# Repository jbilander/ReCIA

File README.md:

# ReCIA
A drop in replacement CIA (8520) for old Amiga Computers

This is WORK IN PROGRESS. If you generate gerbers and order PCBs from this source you are doing so completely at your own risk!.

Current design is based on an intel/altera 10 Max FPGA but this is mostly so we can signal tap and record how a real 8520 behaves.
The oscillator on board is 10 MHz and the PLL on the Max 10 can take this clock and make a perfect 28.375 MHz or a 28.636 MHz clock signal which will be nice to base the logic on instead of the E-CLK.

The final design will probably target a `LCMXO2-640HC-4SG48C` FPGA or a microcontroller such as `AVR128DA64` or a `RP2350`.

When the DIP-version is functional a PLCC-version (for big box Amigas) can be made.

***

<br />

<br />

<br />

***

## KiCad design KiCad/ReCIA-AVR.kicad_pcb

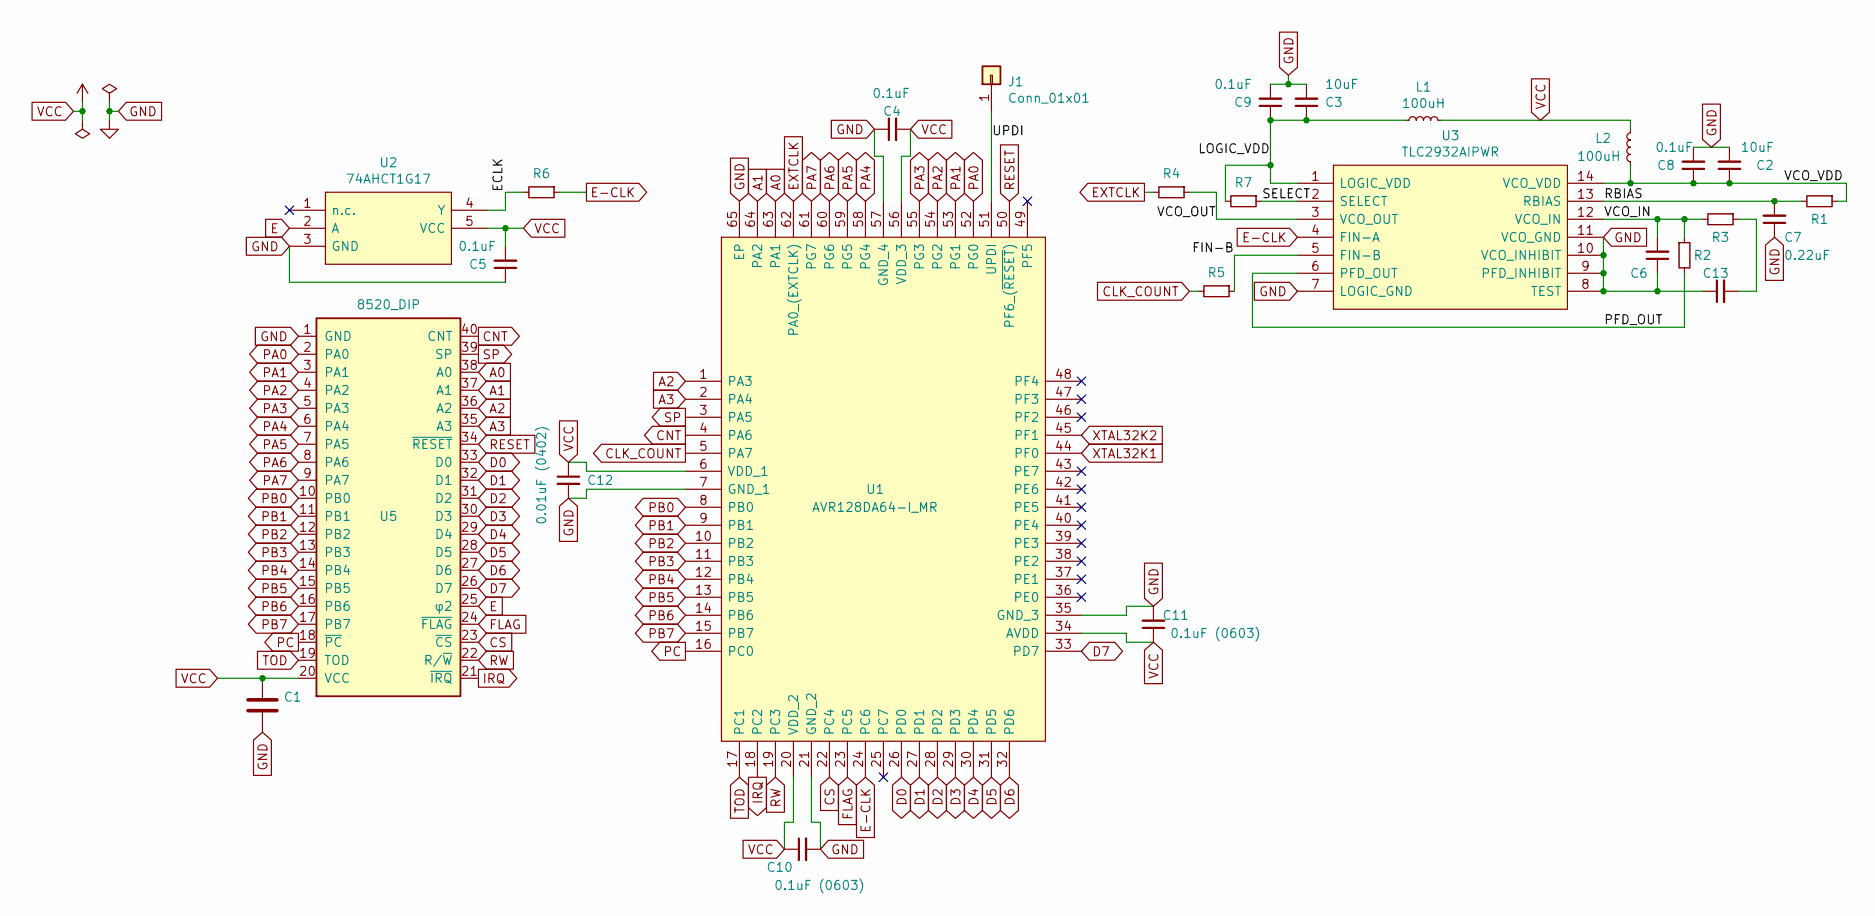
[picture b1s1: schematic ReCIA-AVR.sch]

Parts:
C1: C; C_1206_3216Metric_Pad1.33x1.80mm_HandSolder
C2, C3: 10uF; C_1206_3216Metric_Pad1.33x1.80mm_HandSolder
C4, C5, C6, C8, C9, C13: 0.1uF; C_0603_1608Metric_Pad1.08x0.95mm_HandSolder
C7: 0.22uF; C_0603_1608Metric_Pad1.08x0.95mm_HandSolder
C10, C11: 0.1uF (0603); C_0603_1608Metric_Pad1.08x0.95mm_HandSolder
C12: 0.01uF (0402); C_0402_1005Metric
J1: Conn_01x01; PinHeader_1x01_P2.54mm_Vertical
L1, L2: 100uH; L_0805_2012Metric_Pad1.15x1.40mm_HandSolder
R1: 3k3; R_0603_1608Metric_Pad0.98x0.95mm_HandSolder
R2, R3, R4, R5, R6: 33; R_0603_1608Metric_Pad0.98x0.95mm_HandSolder
R7: 10k; R_0603_1608Metric_Pad0.98x0.95mm_HandSolder
U1: AVR128DA64-I_MR; QFN-64-1EP_9x9mm_P0.5mm_EP7.15x7.15mm_ThermalVias
U2: 74AHCT1G17; SOT95P275X110-5N
U3: TLC2932AIPWR; TSSOP-14_4.4x5mm_P0.65mm
U5: 8520_DIP; DIP-40_W15.24mm

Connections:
/ECLK: R6.2, U2.4 (Y)
/FIN-B: R5.1, U3.5 (FIN-B)
/LOGIC_VDD: C3.1, C9.1, L1.1, R7.2, U3.1 (LOGIC_VDD)
/PFD_OUT: R2.2, U3.6 (PFD_OUT)
/RBIAS: C7.2, R1.2, U3.13 (RBIAS)
/SELECT: R7.1, U3.2 (SELECT)
/UPDI: J1.1, U1.51 (UPDI)
/VCO_IN: C6.2, R2.1, R3.2, U3.12 (VCO_IN)
/VCO_OUT: R4.1, U3.3 (VCO_OUT)
/VCO_VDD: C2.1, C8.1, L2.1, R1.1, U3.14 (VCO_VDD)
A0: U1.63 (PA1), U5.38 (A0)
A1: U1.64 (PA2), U5.37 (A1)
A2: U1.1 (PA3), U5.36 (A2)
A3: U1.2 (PA4), U5.35 (A3)
CLK_COUNT: R5.2, U1.5 (PA7)
CNT: U1.4 (PA6), U5.40 (CNT)
CS: U1.22 (PC4), U5.23 (~CS)
D0: U1.26 (PD0), U5.33 (D0)
D1: U1.27 (PD1), U5.32 (D1)
D2: U1.28 (PD2), U5.31 (D2)
D3: U1.29 (PD3), U5.30 (D3)
D4: U1.30 (PD4), U5.29 (D4)
D5: U1.31 (PD5), U5.28 (D5)
D6: U1.32 (PD6), U5.27 (D6)
D7: U1.33 (PD7), U5.26 (D7)
E: U2.2 (A), U5.25 (φ2)
E-CLK: R6.1, U1.24 (PC6), U3.4 (FIN-A)
EXTCLK: R4.2, U1.62 (PA0_(EXTCLK))
FLAG: U1.23 (PC5), U5.24 (~FLAG)
GND: C1.2, C2.2, C3.2, C4.1, C5.1, C6.1, C7.1, C8.2, C9.2, C10.2, C11.2, C12.2, C13.1, U1.7 (GND_1), U1.21 (GND_2), U1.35 (GND_3), U1.57 (GND_4), U1.65 (EP), U2.3 (GND), U3.7 (LOGIC_GND), U3.8 (TEST), U3.9 (PFD_INHIBIT), U3.10 (VCO_INHIBIT), U3.11 (VCO_GND), U5.1 (GND)
IRQ: U1.18 (PC2), U5.21 (~IRQ)
unnamed: C13.2, R3.1
PA0: U1.52 (PG0), U5.2 (PA0)
PA1: U1.53 (PG1), U5.3 (PA1)
PA2: U1.54 (PG2), U5.4 (PA2)
PA3: U1.55 (PG3), U5.5 (PA3)
PA4: U1.58 (PG4), U5.6 (PA4)
PA5: U1.59 (PG5), U5.7 (PA5)
PA6: U1.60 (PG6), U5.8 (PA6)
PA7: U1.61 (PG7), U5.9 (PA7)
PB0: U1.8 (PB0), U5.10 (PB0)
PB1: U1.9 (PB1), U5.11 (PB1)
PB2: U1.10 (PB2), U5.12 (PB2)
PB3: U1.11 (PB3), U5.13 (PB3)
PB4: U1.12 (PB4), U5.14 (PB4)
PB5: U1.13 (PB5), U5.15 (PB5)
PB6: U1.14 (PB6), U5.16 (PB6)
PB7: U1.15 (PB7), U5.17 (PB7)
PC: U1.16 (PC0), U5.18 (~PC)
RESET: U1.50 (PF6_(~RESET)), U5.34 (~RESET)
RW: U1.19 (PC3), U5.22 (R/~W)
SP: U1.3 (PA5), U5.39 (SP)
TOD: U1.17 (PC1), U5.19 (TOD)
VCC: C1.1, C4.2, C5.2, C10.1, C11.1, C12.1, L1.2, L2.2, U1.6 (VDD_1), U1.20 (VDD_2), U1.34 (AVDD), U1.56 (VDD_3), U2.5 (VCC), U5.20 (VCC)
XTAL32K1: U1.44 (PF0)
XTAL32K2: U1.45 (PF1)

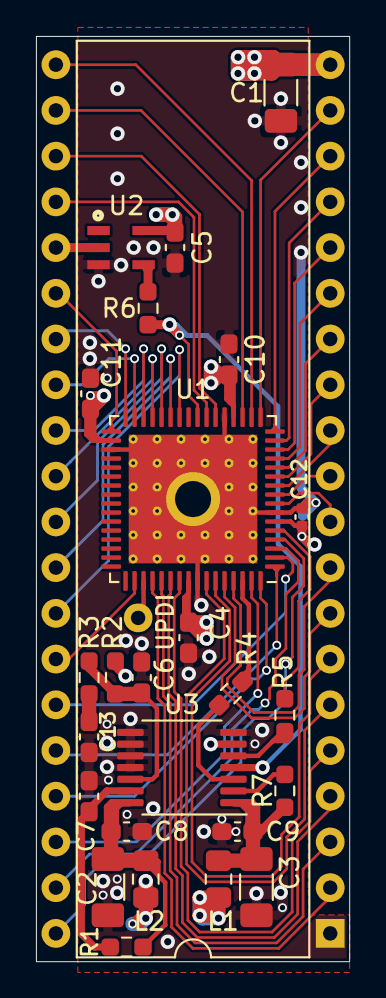
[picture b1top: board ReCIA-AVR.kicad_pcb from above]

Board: 4 copper layers, 17.4 x 51.4 mm, 27 parts (0 on the bottom side), 54 nets.

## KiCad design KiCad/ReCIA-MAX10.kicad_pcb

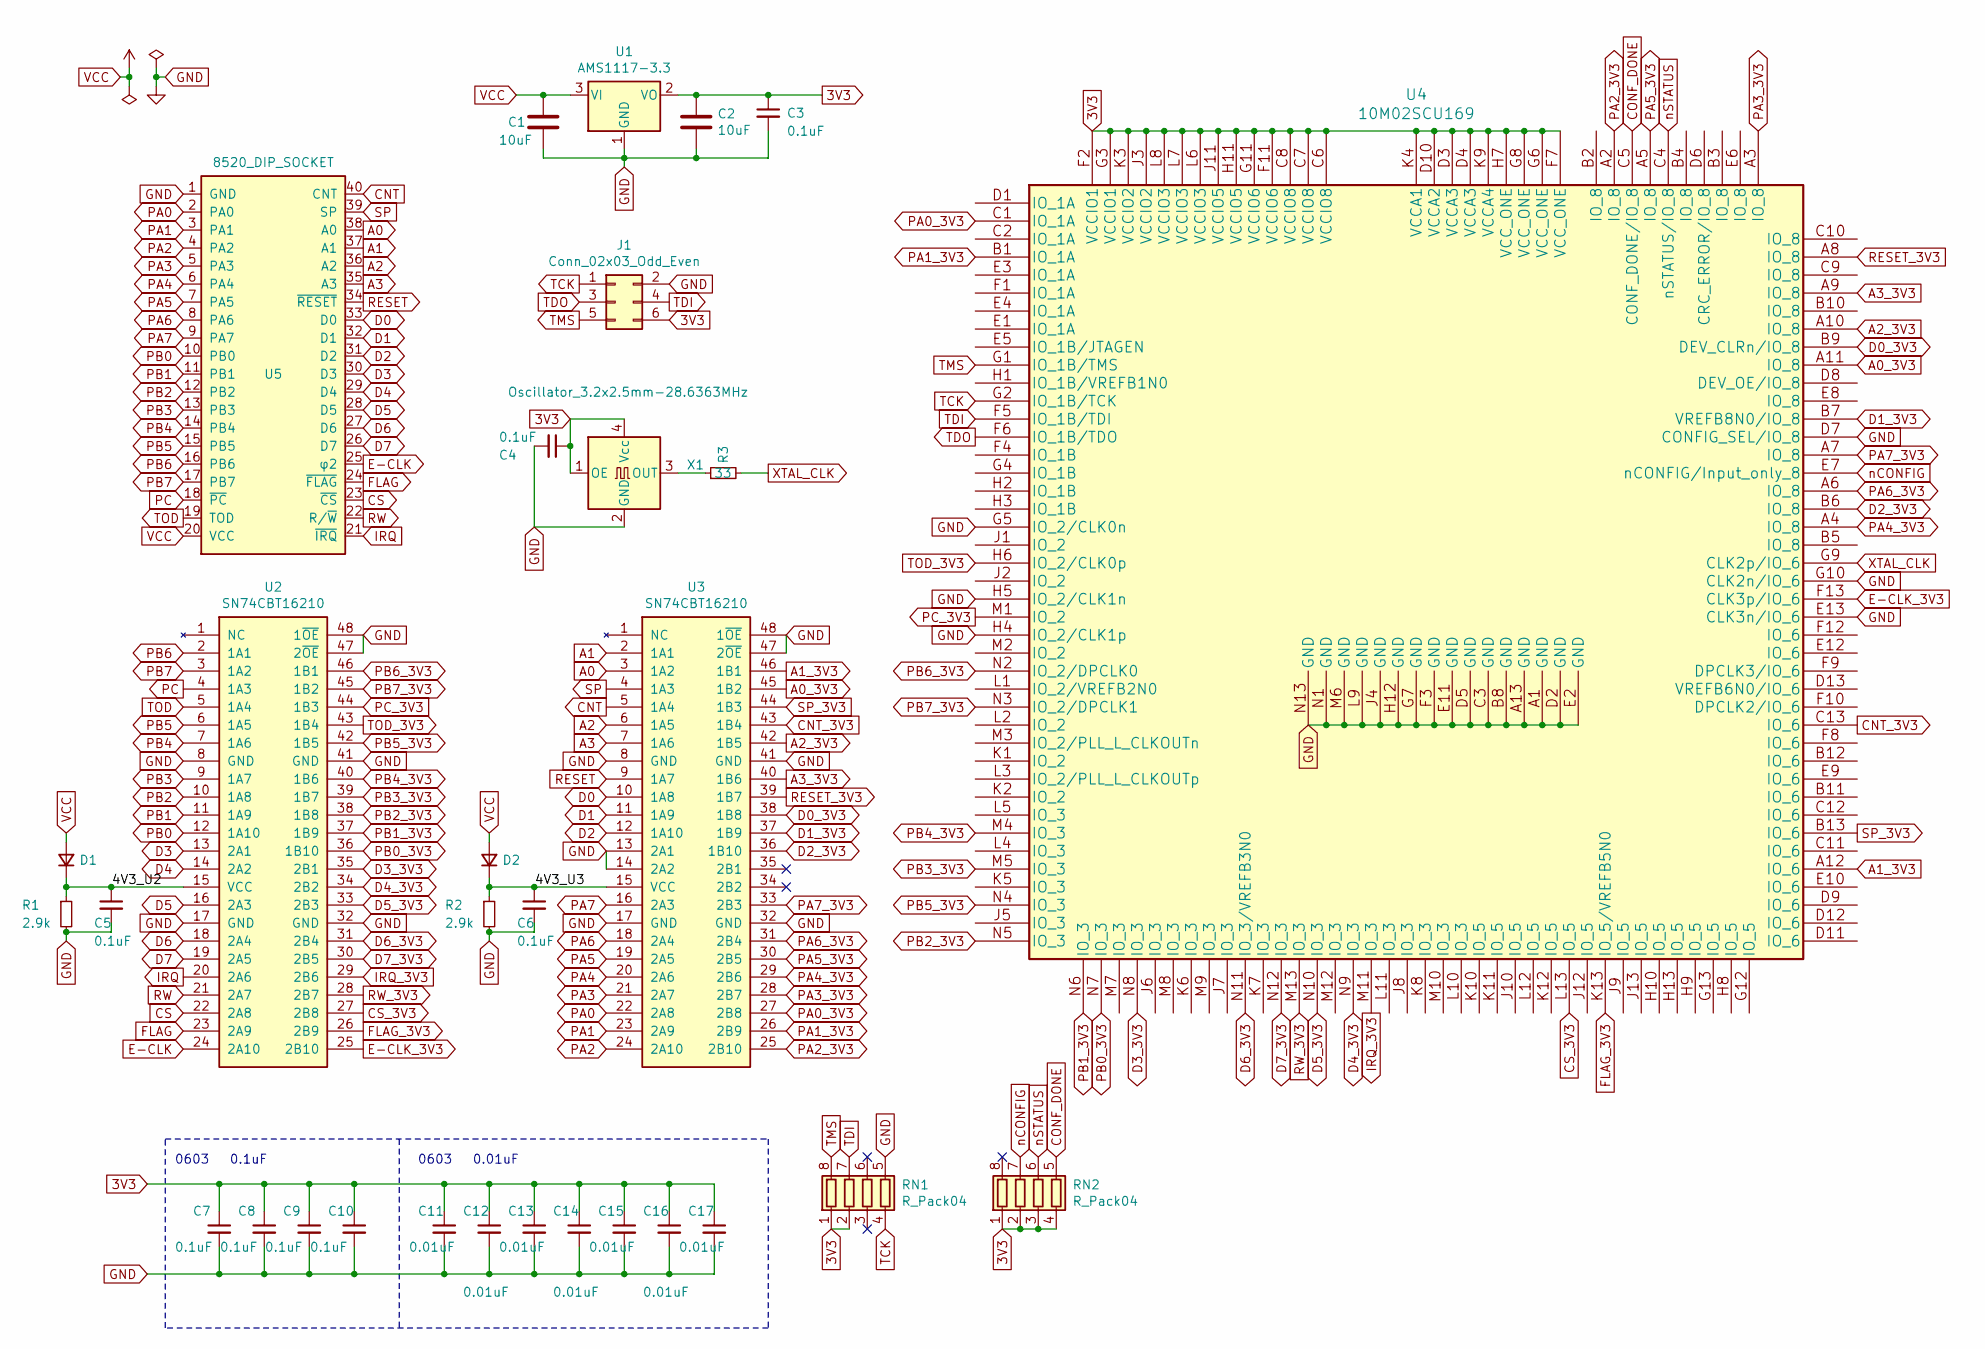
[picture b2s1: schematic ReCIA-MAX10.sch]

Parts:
C1, C2: 10uF; C_1206_3216Metric_Pad1.33x1.80mm_HandSolder
C3: 0.1uF; C_0805_2012Metric_Pad1.18x1.45mm_HandSolder
C4: 0.1uF; C_0805_2012Metric
C5, C6, C7, C8, C9: 0.1uF; C_0603_1608Metric_Pad1.08x0.95mm_HandSolder
C10: 0.1uF; C_0603_1608Metric
C11, C12, C13, C14, C15: 0.01uF; C_0603_1608Metric_Pad1.08x0.95mm_HandSolder
C16, C17: 0.01uF; C_0603_1608Metric
D1, D2: D_Small; D_0603_1608Metric_Pad1.05x0.95mm_HandSolder
J1: Conn_02x03_Odd_Even; PinHeader_2x03_P2.00mm_Vertical_SMD
R1, R2: 2.9k; R_0603_1608Metric_Pad0.98x0.95mm_HandSolder
R3: 33; R_0603_1608Metric_Pad0.98x0.95mm_HandSolder
RN1, RN2: R_Pack04; RESCAF80P320X160X60-8N
U1: AMS1117-3.3; SOT-223-3_TabPin2
U2, U3: SN74CBT16210; TSSOP-48_4.4x9.7mm_P0.4mm
U4: 10M02SCU169; BGA-169_11.0x11.0mm_Layout13x13_P0.8mm_Ball0.5mm_Pad0.35mm_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
U5: 8520_DIP_SOCKET; DIP-40_W15.24mm
X1: Oscillator_3.2x2.5mm-28.6363MHz; Oscillator_SMD_SeikoEpson_SG8002CE-4Pin_3.2x2.5mm

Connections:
3V3: C2.1, C3.1, C4.1, C7.1, C8.1, C9.1, C10.1, C11.1, C12.1, C13.1, C14.1, C15.1, C16.1, C17.1, J1.6, RN1.1 (R1.1), RN1.2 (R2.1), RN2.1 (R1.1), RN2.2 (R2.1), RN2.3 (R3.1), RN2.4 (R4.1), U1.2 (VO), U4.C6 (VCCIO8), U4.C7 (VCCIO8), U4.C8 (VCCIO8), U4.D3 (VCCA3), U4.D4 (VCCA3), U4.D10 (VCCA2), U4.F2 (VCCIO1), U4.F7 (VCC_ONE), U4.F11 (VCCIO6), U4.G3 (VCCIO1), U4.G6 (VCC_ONE), U4.G8 (VCC_ONE), U4.G11 (VCCIO6), U4.H7 (VCC_ONE), U4.H11 (VCCIO5), U4.J3 (VCCIO2), U4.J11 (VCCIO5), U4.K3 (VCCIO2), U4.K4 (VCCA1), U4.K9 (VCCA4), U4.L6 (VCCIO3), U4.L7 (VCCIO3), U4.L8 (VCCIO3), X1.1 (OE), X1.4 (Vcc)
/4V3_U2: C5.1, D1.1 (K), R1.1, U2.15 (VCC)
/4V3_U3: C6.1, D2.1 (K), R2.1, U3.15 (VCC)
A0: U3.3 (1A2), U5.38 (A0)
A0_3V3: U3.45 (1B2), U4.A11 (IO_8)
A1: U3.2 (1A1), U5.37 (A1)
A1_3V3: U3.46 (1B1), U4.A12 (IO_6)
A2: U3.6 (1A5), U5.36 (A2)
A2_3V3: U3.42 (1B5), U4.A10 (IO_8)
A3: U3.7 (1A6), U5.35 (A3)
A3_3V3: U3.40 (1B6), U4.A9 (IO_8)
CNT: U3.5 (1A4), U5.40 (CNT)
CNT_3V3: U3.43 (1B4), U4.C13 (IO_6)
CONF_DONE: RN2.5 (R4.2), U4.C5 (CONF_DONE/IO_8)
CS: U2.22 (2A8), U5.23 (~CS)
CS_3V3: U2.27 (2B8), U4.L13 (IO_5)
D0: U3.10 (1A8), U5.33 (D0)
D0_3V3: U3.38 (1B8), U4.B9 (DEV_CLRn/IO_8)
D1: U3.11 (1A9), U5.32 (D1)
D1_3V3: U3.37 (1B9), U4.B7 (VREFB8N0/IO_8)
D2: U3.12 (1A10), U5.31 (D2)
D2_3V3: U3.36 (1B10), U4.B6 (IO_8)
D3: U2.13 (2A1), U5.30 (D3)
D3_3V3: U2.35 (2B1), U4.N8 (IO_3)
D4: U2.14 (2A2), U5.29 (D4)
D4_3V3: U2.34 (2B2), U4.N9 (IO_3)
D5: U2.16 (2A3), U5.28 (D5)
D5_3V3: U2.33 (2B3), U4.N10 (IO_3)
D6: U2.18 (2A4), U5.27 (D6)
D6_3V3: U2.31 (2B4), U4.N11 (IO_3/VREFB3N0)
D7: U2.19 (2A5), U5.26 (D7)
D7_3V3: U2.30 (2B5), U4.N12 (IO_3)
E-CLK: U2.24 (2A10), U5.25 (φ2)
E-CLK_3V3: U2.25 (2B10), U4.F13 (CLK3p/IO_6)
FLAG: U2.23 (2A9), U5.24 (~FLAG)
FLAG_3V3: U2.26 (2B9), U4.K13 (IO_5/VREFB5N0)
GND: C1.2, C2.2, C3.2, C4.2, C5.2, C6.2, C7.2, C8.2, C9.2, C10.2, C11.2, C12.2, C13.2, C14.2, C15.2, C16.2, C17.2, J1.2, R1.2, R2.2, RN1.5 (R4.2), U1.1 (GND), U2.8 (GND), U2.17 (GND), U2.32 (GND), U2.41 (GND), U2.47 (2~OE), U2.48 (1~OE), U3.8 (GND), U3.13 (2A1), U3.14 (2A2), U3.17 (GND), U3.32 (GND), U3.41 (GND), U3.47 (2~OE), U3.48 (1~OE), U4.A1 (GND), U4.A13 (GND), U4.B8 (GND), U4.C3 (GND), U4.D2 (GND), U4.D5 (GND), U4.D7 (CONFIG_SEL/IO_8), U4.E2 (GND), U4.E11 (GND), U4.E13 (CLK3n/IO_6), U4.F3 (GND), U4.G5 (IO_2/CLK0n), U4.G7 (GND), U4.G10 (CLK2n/IO_6), U4.H4 (IO_2/CLK1p), U4.H5 (IO_2/CLK1n), U4.H12 (GND), U4.J4 (GND), U4.L9 (GND), U4.M6 (GND), U4.N1 (GND), U4.N13 (GND), U5.1 (GND), X1.2 (GND)
IRQ: U2.20 (2A6), U5.21 (~IRQ)
IRQ_3V3: U2.29 (2B6), U4.M11 (IO_3)
unnamed: R3.1, X1.3 (OUT)
PA0: U3.22 (2A8), U5.2 (PA0)
PA0_3V3: U3.27 (2B8), U4.C1 (IO_1A)
PA1: U3.23 (2A9), U5.3 (PA1)
PA1_3V3: U3.26 (2B9), U4.B1 (IO_1A)
PA2: U3.24 (2A10), U5.4 (PA2)
PA2_3V3: U3.25 (2B10), U4.A2 (IO_8)
PA3: U3.21 (2A7), U5.5 (PA3)
PA3_3V3: U3.28 (2B7), U4.A3 (IO_8)
PA4: U3.20 (2A6), U5.6 (PA4)
PA4_3V3: U3.29 (2B6), U4.A4 (IO_8)
PA5: U3.19 (2A5), U5.7 (PA5)
PA5_3V3: U3.30 (2B5), U4.A5 (IO_8)
PA6: U3.18 (2A4), U5.8 (PA6)
PA6_3V3: U3.31 (2B4), U4.A6 (IO_8)
PA7: U3.16 (2A3), U5.9 (PA7)
PA7_3V3: U3.33 (2B3), U4.A7 (IO_8)
PB0: U2.12 (1A10), U5.10 (PB0)
PB0_3V3: U2.36 (1B10), U4.N7 (IO_3)
PB1: U2.11 (1A9), U5.11 (PB1)
PB1_3V3: U2.37 (1B9), U4.N6 (IO_3)
PB2: U2.10 (1A8), U5.12 (PB2)
PB2_3V3: U2.38 (1B8), U4.N5 (IO_3)
PB3: U2.9 (1A7), U5.13 (PB3)
PB3_3V3: U2.39 (1B7), U4.M5 (IO_3)
PB4: U2.7 (1A6), U5.14 (PB4)
PB4_3V3: U2.40 (1B6), U4.M4 (IO_3)
PB5: U2.6 (1A5), U5.15 (PB5)
PB5_3V3: U2.42 (1B5), U4.N4 (IO_3)
PB6: U2.2 (1A1), U5.16 (PB6)
PB6_3V3: U2.46 (1B1), U4.N2 (IO_2/DPCLK0)
PB7: U2.3 (1A2), U5.17 (PB7)
PB7_3V3: U2.45 (1B2), U4.N3 (IO_2/DPCLK1)
PC: U2.4 (1A3), U5.18 (~PC)
PC_3V3: U2.44 (1B3), U4.M1 (IO_2)
RESET: U3.9 (1A7), U5.34 (~RESET)
RESET_3V3: U3.39 (1B7), U4.A8 (IO_8)
RW: U2.21 (2A7), U5.22 (R/~W)
RW_3V3: U2.28 (2B7), U4.M13 (IO_3)
SP: U3.4 (1A3), U5.39 (SP)
SP_3V3: U3.44 (1B3), U4.B13 (IO_6)
TCK: J1.1, RN1.4 (R4.1), U4.G2 (IO_1B/TCK)
TDI: J1.4, RN1.7 (R2.2), U4.F5 (IO_1B/TDI)
TDO: J1.3, U4.F6 (IO_1B/TDO)
TMS: J1.5, RN1.8 (R1.2), U4.G1 (IO_1B/TMS)
TOD: U2.5 (1A4), U5.19 (TOD)
TOD_3V3: U2.43 (1B4), U4.H6 (IO_2/CLK0p)
VCC: C1.1, D1.2 (A), D2.2 (A), U1.3 (VI), U5.20 (VCC)
XTAL_CLK: R3.2, U4.G9 (CLK2p/IO_6)
nCONFIG: RN2.7 (R2.2), U4.E7 (nCONFIG/Input_only_8)
nSTATUS: RN2.6 (R3.2), U4.C4 (nSTATUS/IO_8)

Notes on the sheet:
0603 0.1uF
0603 0.01uF

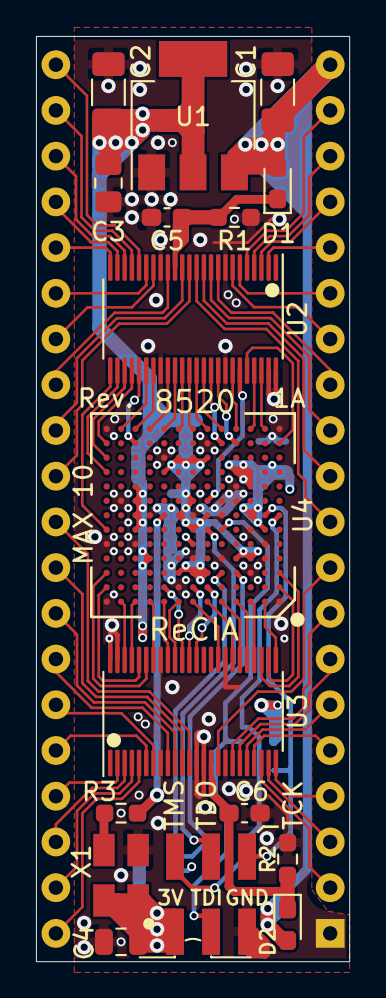
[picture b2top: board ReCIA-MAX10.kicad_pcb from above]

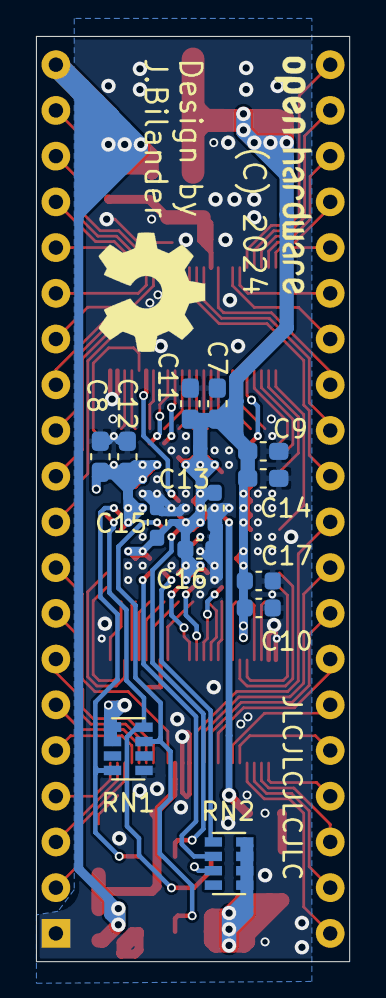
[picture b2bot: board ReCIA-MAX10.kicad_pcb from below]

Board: 4 copper layers, 17.4 x 51.4 mm, 31 parts (13 on the bottom side), 90 nets.

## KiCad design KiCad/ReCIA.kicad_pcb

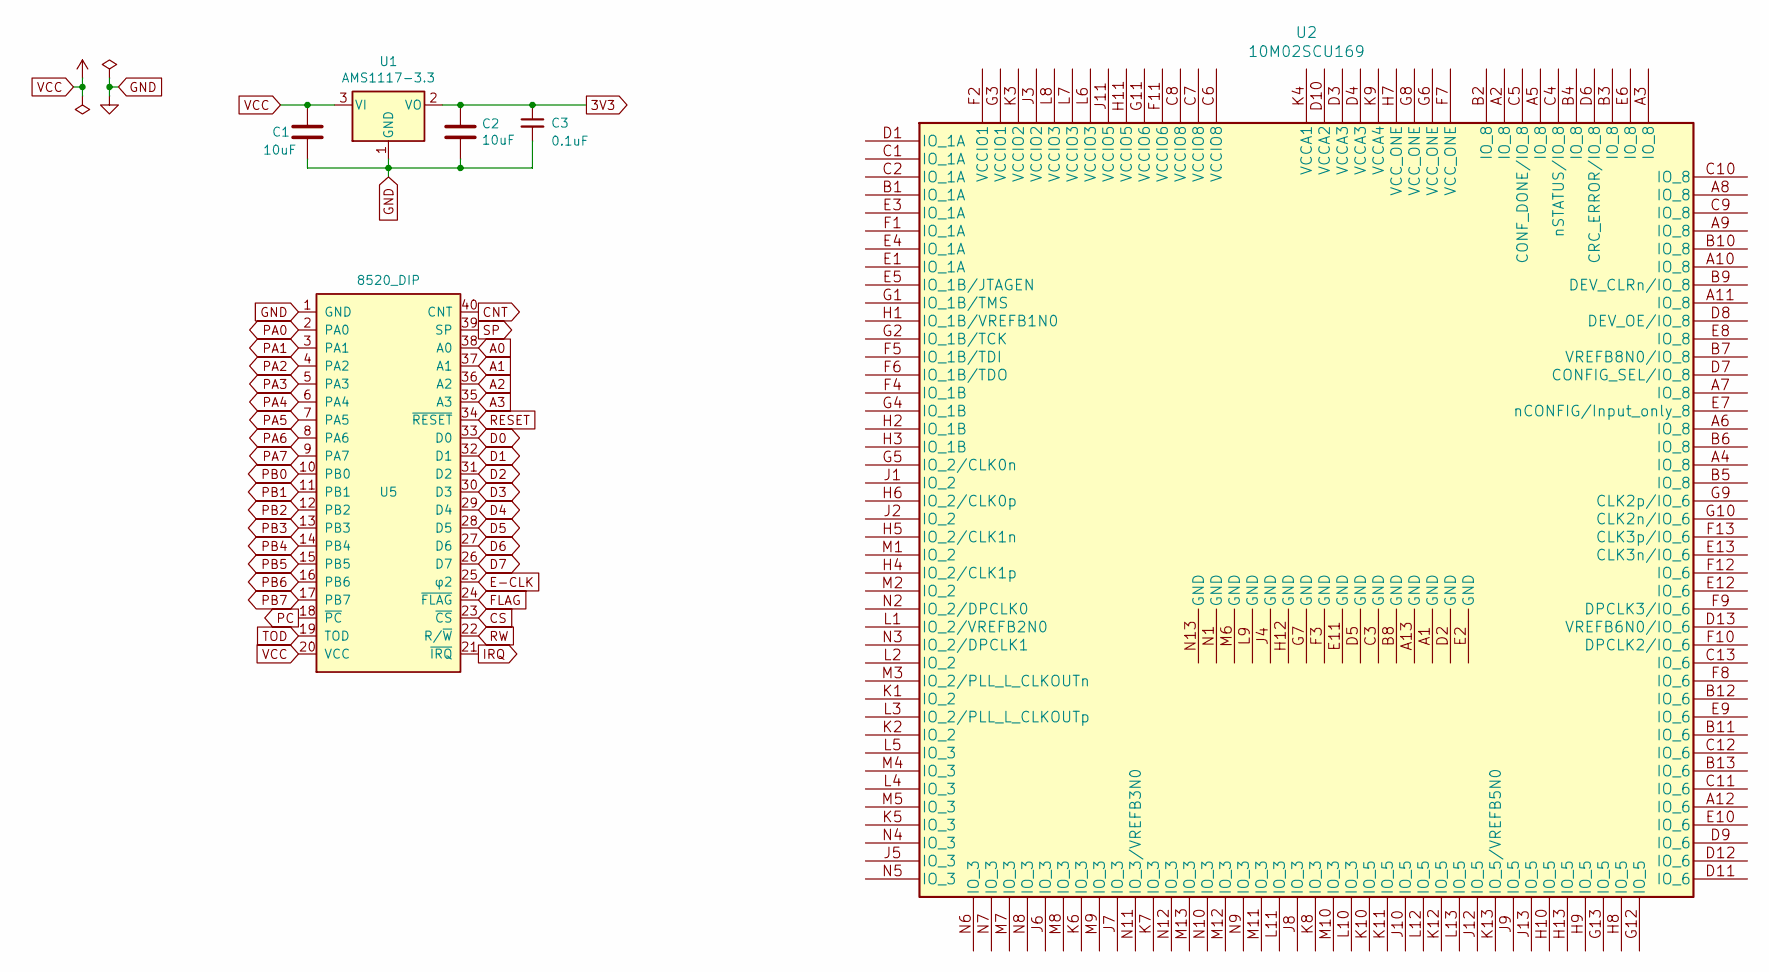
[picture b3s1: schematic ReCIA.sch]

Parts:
C1, C2: 10uF; C_1206_3216Metric_Pad1.33x1.80mm_HandSolder
C3: 0.1uF; C_0805_2012Metric_Pad1.18x1.45mm_HandSolder
U1: AMS1117-3.3; SOT-223-3_TabPin2
U2: 10M02SCU169; BGA-169_11.0x11.0mm_Layout13x13_P0.8mm_Ball0.5mm_Pad0.35mm_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
U5: 8520_DIP; DIP-40_W15.24mm

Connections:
3V3: C2.1, C3.1, U1.2 (VO)
A0: U5.38 (A0)
A1: U5.37 (A1)
A2: U5.36 (A2)
A3: U5.35 (A3)
CNT: U5.40 (CNT)
CS: U5.23 (~CS)
D0: U5.33 (D0)
D1: U5.32 (D1)
D2: U5.31 (D2)
D3: U5.30 (D3)
D4: U5.29 (D4)
D5: U5.28 (D5)
D6: U5.27 (D6)
D7: U5.26 (D7)
E-CLK: U5.25 (φ2)
FLAG: U5.24 (~FLAG)
GND: C1.2, C2.2, C3.2, U1.1 (GND), U5.1 (GND)
IRQ: U5.21 (~IRQ)
PA0: U5.2 (PA0)
PA1: U5.3 (PA1)
PA2: U5.4 (PA2)
PA3: U5.5 (PA3)
PA4: U5.6 (PA4)
PA5: U5.7 (PA5)
PA6: U5.8 (PA6)
PA7: U5.9 (PA7)
PB0: U5.10 (PB0)
PB1: U5.11 (PB1)
PB2: U5.12 (PB2)
PB3: U5.13 (PB3)
PB4: U5.14 (PB4)
PB5: U5.15 (PB5)
PB6: U5.16 (PB6)
PB7: U5.17 (PB7)
PC: U5.18 (~PC)
RESET: U5.34 (~RESET)
RW: U5.22 (R/~W)
SP: U5.39 (SP)
TOD: U5.19 (TOD)
VCC: C1.1, U1.3 (VI), U5.20 (VCC)

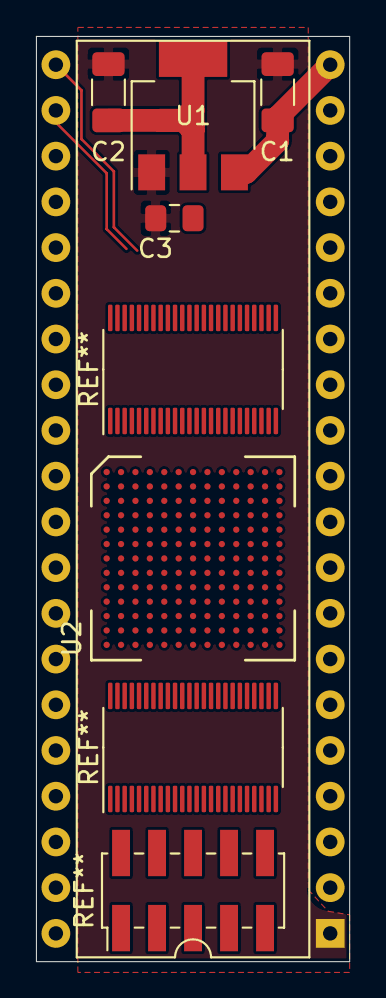
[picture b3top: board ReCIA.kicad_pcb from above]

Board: 4 copper layers, 17.4 x 51.4 mm, 6 parts (0 on the bottom side), 3 nets.

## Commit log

2024-08-15 Add KiCad files
2024-08-15 Changed to four layers and fixed clearance and default settings for traces and vias etc
2024-08-15 update symbol
2024-08-15 Add nets
2024-08-16 Updated file
2024-08-16 Added a 3.3V LDO Voltage Regulator
2024-08-19 Add footprint
2024-08-19 add file
2024-08-19 Add 10 Max FPGA
2024-08-21 Add AVR128DA64-I_MR symbol
2024-08-21 Add 3D-model of AVR128DA64-I_MR
2024-08-21 Add KiCad files for AVR-version
2024-08-21 Add QFN-80 footprint
2024-08-21 Add KiCad files for Max10 version
2024-08-21 Add KiCad lib for Max10 version
2024-08-26 Add FET bus-switch level shifters SN74CBT16210
2024-08-26 Add JTAG-header
2024-08-27 more routing and pin assignment
2024-08-27 routing JTAG plus more routing of power to BGA chip
2024-08-27 add XTAL to design
2024-08-27 add XTAL step file to 3D Setting for X1
2024-08-27 add 15 mil trace
2024-08-27 re-routed XTAL trace with 15 mil trace
2024-08-27 more routing, pin assignments and silkscreen fixes
2024-08-28 more pin assignments and routing
2024-08-28 more power routing, vias and silkscreen fixes
2024-08-28 Changed to minimum width to 0.14 mm for front F.Cu zone and solid pad connection to zone for BGA-footprint.
2024-08-28 Silkscreen fixes, add dot indicator for pin 1 on U2,U3,U4
2024-08-28 Add pin assignment and routing for D0,D1,D2 to the FPGA
2024-08-29 Add decoupling caps for FPGA-chip
2024-08-30 Add more decoupling caps for FPGA-chip
2024-08-30 Assign GND to CONFIG_SEL pad
2024-08-30 Add nCONFIG signal
2024-08-30 Add nSTATUS signal
2024-08-30 Add CONF_DONE signal
2024-08-31 add 3d model for resistor pack
2024-08-31 add footprint for resistor pack
2024-08-31 Add 10k resistor pack RN1 and assign pull-ups for TMS, TDI and pull-down for TCK
2024-08-31 Add 10k resistor pack RN2 with pull-ups for CONF_DONE, nSTATUS, nCONFIG
2024-09-01 small fix 3V3-routing
2024-09-02 Assign H4,H5 pad to GND
2024-09-02 Add silkscreen texts
2024-09-02 corrected smalles via size to 0.45mm/0.2mm
2024-12-26 add images
2024-12-26 Rename ReCIA-Max10_pic2.JPG to ReCIA-Max10_pic2.jpg
2024-12-29 Pin assignment of A0-A3, SP, CNT signals for the AVR-version and more routing done
2025-01-05 add 74AHCT1G17 symbol
2025-01-05 Add a 74AHCT1G17 - Single Schmitt trigger buffer for the E-CLK on the AVR version
2025-01-05 Add decoupling cap for 74AHCT1G17 on the AVR version
2025-01-05 Add a 33 Ohm damping resistor on the E-CLK buffer out line
2025-01-05 Add TLC2932AIPWR to the AVR version
2025-01-05 Add 10uF 1206 capacitor on VCC input for the AVR version
2025-01-12 Fixed placement of PLL-chip and added inductor and caps for power supply pins Logic VDD and VCO VDD for the AVR-version
2025-01-12 Add 33 Ohm damping resistor on EXTCLK-line
2025-01-12 Add net and resistor between PDF_OUT and VCO_IN for the AVR-version
2025-01-12 Add resistor and net for PLL FIN-B clk-count input signal from AVR pin 5 (PA7)
2025-01-12 Add 0.4 mm track width
2025-01-12 Add pull-up resistor on SELECT-line and more placement and routing fixes
2025-01-14 Add 3.3k resistor and 0.22uF cap for the RBIAS-pin on the PLL
2025-01-14 Add cap for the VCO_IN-pin on the PLL
2025-01-16 Change from 0805 to 1206 size on C2 and C3
2025-01-16 Add resistor and cap on VCO_IN line
2025-01-17 Fixed caps and resistor references enumeration, more routing and small fixes positioning vias
2025-01-18 corrected C8,C9 to 0.1uF
2025-01-19 Add UPDI pin-header
2025-01-19 Add annotation UPDI header
